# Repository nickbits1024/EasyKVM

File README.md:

# _Easy KVM_

## About Easy KVM

Easy KVM is a Wi-Fi enabled hybrid KVM.  It acts a an USB sharing switch and VESA DDC/CI switcher.  It does not touch the video signal which eliminates a lot of issues found with standard KVMs.

## Features

* Single USB 2.0 high speed capable port to be used with an external USB hub
* Wi-Fi control
* HDMI passthrough
* USB keyboard for macros and port switching
* Control monitor power state
* Integrated with Home Assistant

## External Requirements
* USB macro keypad e.g. [Amazon](https://www.amazon.com/gp/product/B09CKT8B7Y) [AliExpress](https://www.aliexpress.us/item/3256804248423460.html)
* USB 2.0 high speed hub e.g. [Amazon](https://www.amazon.com/gp/product/B005A0B3FG)
* Monitor with an HDMI port that supports VESA DDC/CI

## Port Setup
1. Connect source HDMI cable from video card to either one of the HDMI ports
2. Connect other HDMI port to monitor
3. Connect J1 Micro USB (top left) to PC1 USB
4. Connect J2 Micro USB (top right) to PC2 USB
5. Connect J6 Micro USB (bottom renter) to macro keypad
6. Connect J7 USB (bottom right) to USB hub
7. Connect J4 Micro USB (Center right) to either USB power or PC (for programming and serial monitoring)

## Wi-Fi Setup
Wi-Fi network selection is done through bluetooth.  
1. Download nRF Connect and connect to KVM
2. Open the client services tab and click Write Value the (up arrow) on the characteristic ending with an UUID of 29.  

3. Click the UTF-8 tab and enter the network SSID and click Write.

4. Click Write Value on the characteristic ending in 01.  This is the Wi-Fi password.  After clicking Write, the KVM should connect to the network.

## WebServer End Points

| URL | Method | Function | Payload |
| --- | ------ | -------- | ------- |
|/config|GET|Open configuration page||
|/monitor|GET|Return monitor state|`{	"on":	true }`|
|/monitor|POST|Set monitor state|`{	"on":	true }`|
|/kvm|GET|Return selected KVM port|`{ "kvm":	1 }`|
|/kvm/1|GET|Select KVM port 1||
|/kvm/2|GET|Select KVM port 2||

## Home Assistant
The KVM needs a Long-Lived Access Token to interact with home assistant.  Create one from the home assistant profile page and save it for later (e.g. notepad)

### Monitor Switch

Copy code below into the home assistant switches.yaml file.  This will create a switch in home assistant that can be used to turn the connected monitor on and off.
```
- platform: rest
  name: "Office Monitor"
  unique_id: 08a5830e-3309-4998-9d17-7ea7ecf154fd
  resource: http://<<KVM_HOST_NAME_OR_IP>>/monitor
  timeout: 30
  body_on: '{"on": true}'
  body_off: '{"on": false}'
  is_on_template: "{{ value_json.on }}"
  headers:
    Content-Type: application/json
```

## Configuration
1. Determine the IP of the KVM either from router UI or connecting the KVM to a computer and viewing the serial output.
2. Navigate to http://KVM_IP/config
3. Select the desired source and RGB led color for each input
4. Enter home assistant URL and previously created access token
5. Configure the macro keypad functions
6. Click save

Note clipboard import/export only work if you have the KVM behind an https proxy

## Usage
Once properly configured, the inputs can be switched using the configured macro keypad button or through the web server end points

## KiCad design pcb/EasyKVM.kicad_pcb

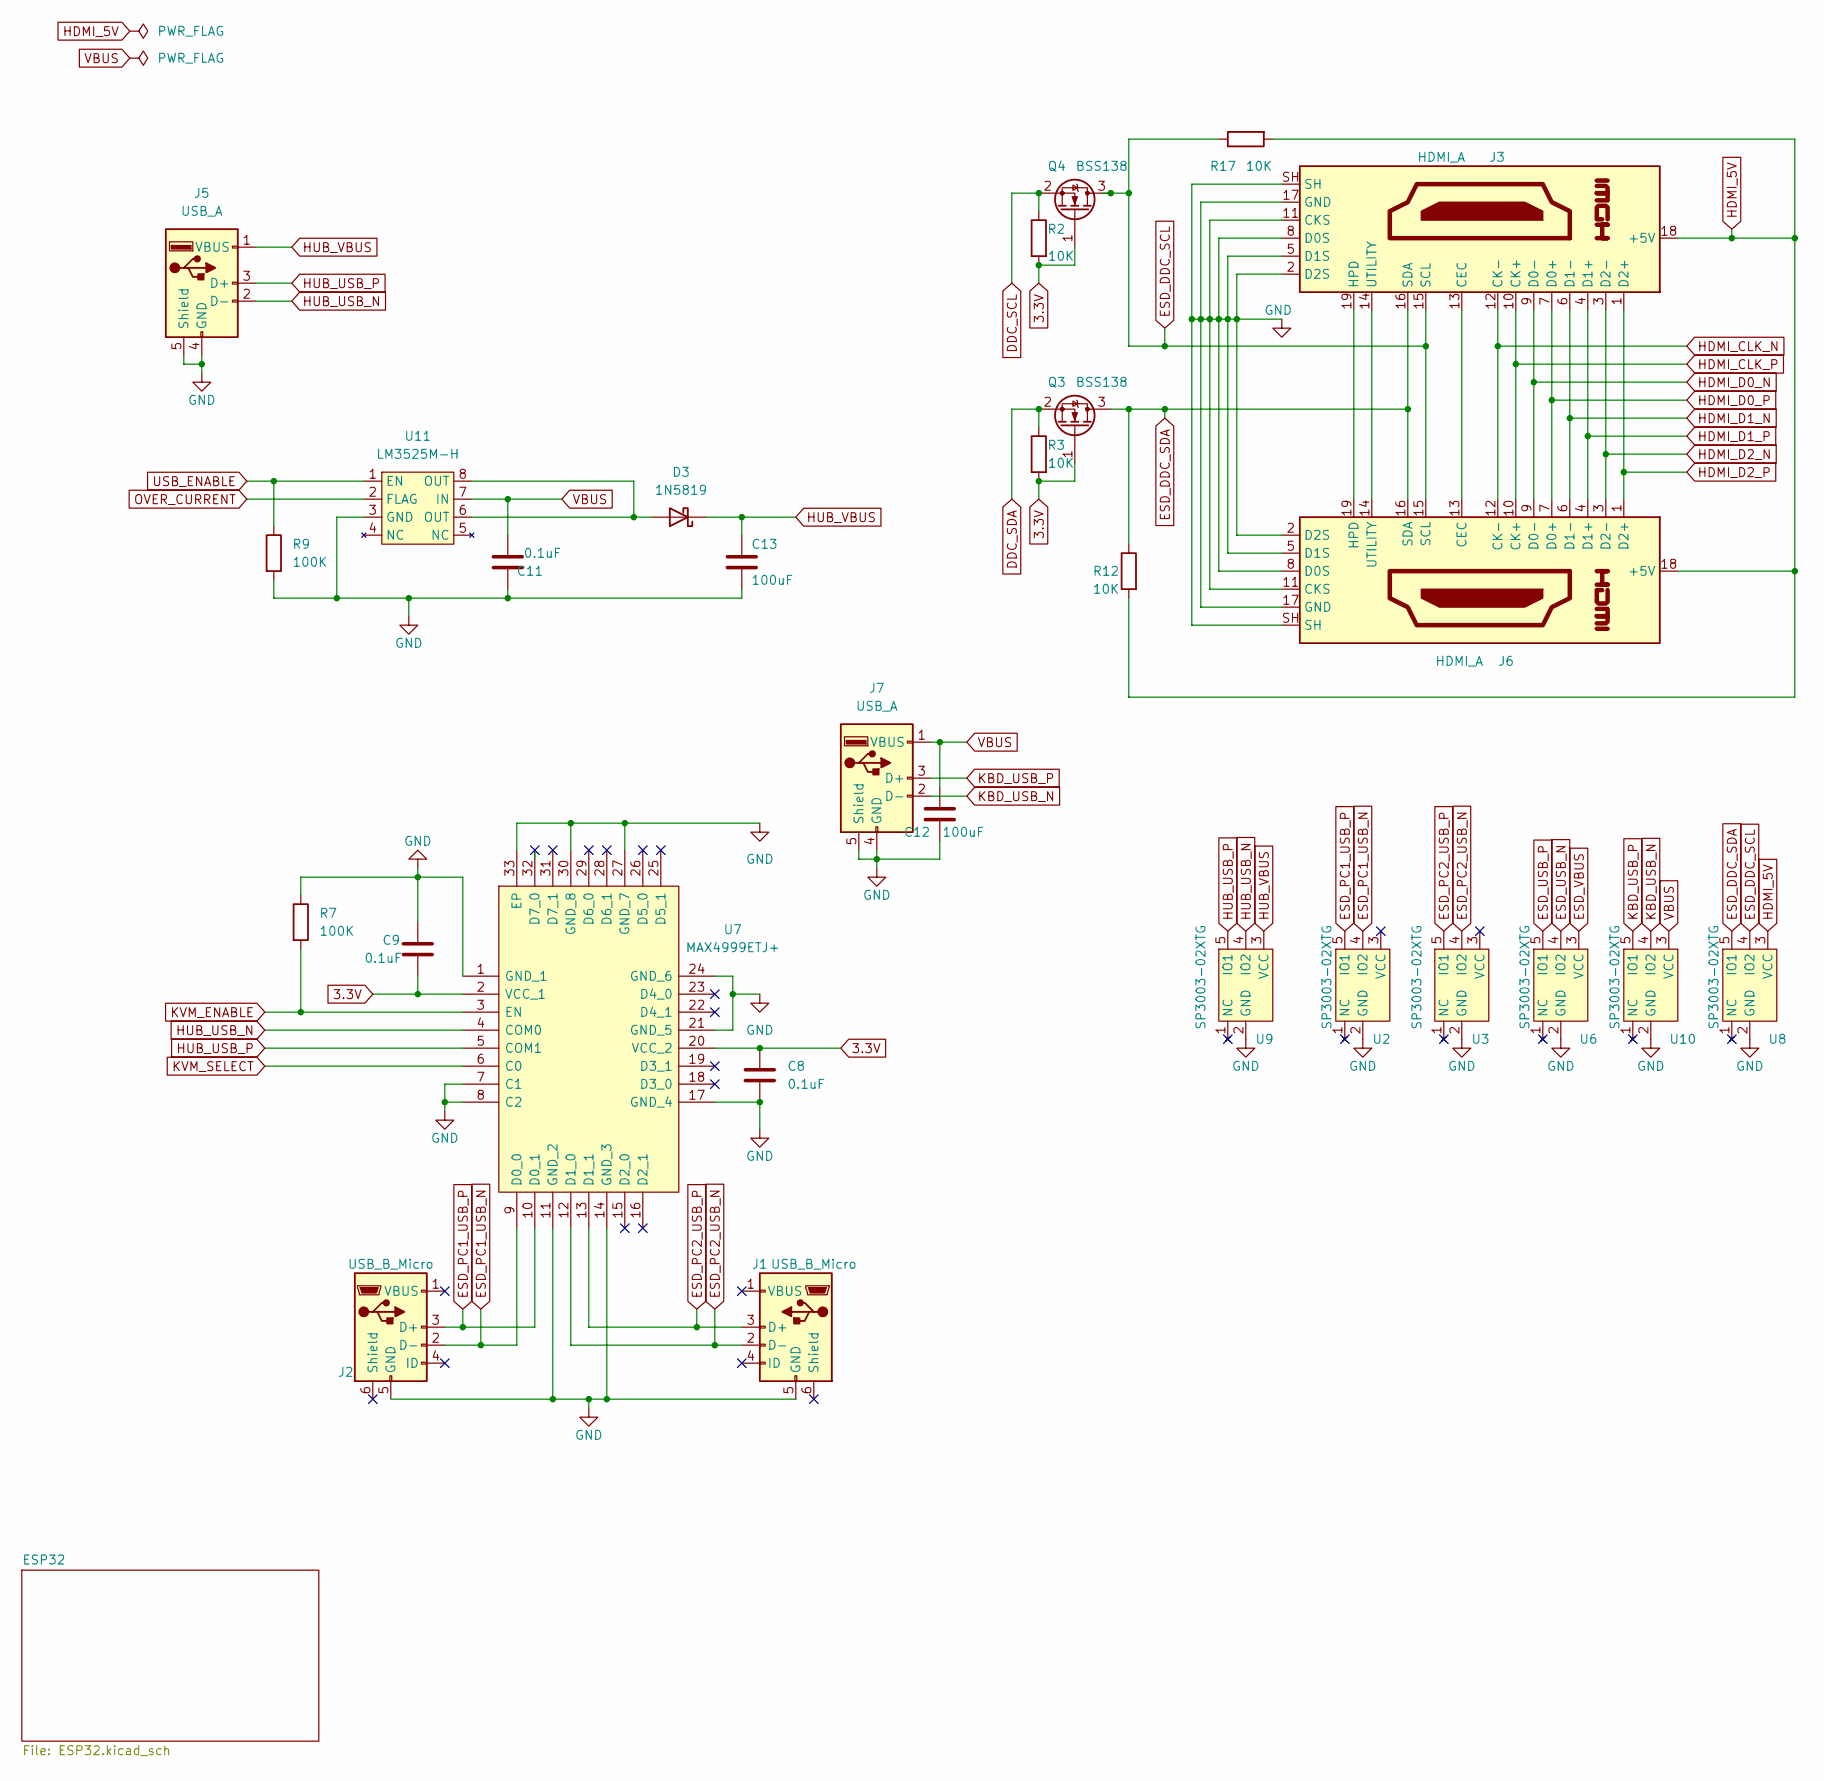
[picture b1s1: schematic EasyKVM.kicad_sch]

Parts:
C8, C9, C11: 0.1uF; C_0603_1608Metric
C12, C13: 100uF; C_1206_3216Metric
D3: 1N5819; D_SOD-323
J1, J2: USB_B_Micro; USB_Micro-B_Molex-105017-0001
J3, J6: HDMI_A; 2086581051
J5, J7: USB_A; USB_A_Molex_67643_Horizontal
Q3, Q4: BSS138; SOT-323_SC-70
R2, R3, R12, R17: 10K; R_0603_1608Metric
R7, R9: 100K; R_0603_1608Metric
U2, U3, U6, U8, U9, U10: SP3003-02XTG; Diodes_SOT-553
U7: MAX4999ETJ+; QFN50P500X500X80-33N; Manufacturer_Part_Number MAX4999ETJ+; Mouser Part Number 700-MAX4999ETJ
U11: LM3525M-H; SOIC-8_3.9x4.9mm_P1.27mm

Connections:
3.3V: C8.2, C9.1, Q3.1 (G), Q4.1 (G), R2.2, R3.2, U7.2 (VCC_1), U7.20 (VCC_2); also elsewhere on the board
DDC_SCL: Q4.2 (S), R2.1; also elsewhere on the board
DDC_SDA: Q3.2 (S), R3.1; also elsewhere on the board
ESD_DDC_SCL: J3.15 (SCL), J6.15 (SCL), Q4.3 (D), R17.1, U8.4 (IO2)
ESD_DDC_SDA: J3.16 (SDA), J6.16 (SDA), Q3.3 (D), R12.1, U8.5 (IO1)
ESD_PC1_USB_N: J2.2 (D-), U2.4 (IO2), U7.9 (D0_0)
ESD_PC1_USB_P: J2.3 (D+), U2.5 (IO1), U7.10 (D0_1)
ESD_PC2_USB_N: J1.2 (D-), U3.4 (IO2), U7.12 (D1_0)
ESD_PC2_USB_P: J1.3 (D+), U3.5 (IO1), U7.13 (D1_1)
ESD_USB_N: U6.4 (IO2); also elsewhere on the board
ESD_USB_P: U6.5 (IO1); also elsewhere on the board
ESD_VBUS: U6.3 (VCC); also elsewhere on the board
GND: C8.1, C9.2, C11.2, C12.2, C13.1, J1.5 (GND), J2.5 (GND), J3.2 (D2S), J3.5 (D1S), J3.8 (D0S), J3.11 (CKS), J3.17 (GND), J3.SH, J5.4 (GND), J5.5 (Shield), J6.2 (D2S), J6.5 (D1S), J6.8 (D0S), J6.11 (CKS), J6.17 (GND), J6.SH, J7.4 (GND), J7.5 (Shield), R7.1, R9.2, U2.2 (GND), U3.2 (GND), U6.2 (GND), U7.1 (GND_1), U7.7 (C1), U7.8 (C2), U7.11 (GND_2), U7.14 (GND_3), U7.17 (GND_4), U7.21 (GND_5), U7.24 (GND_6), U7.27 (GND_7), U7.30 (GND_8), U7.33 (EP), U8.2 (GND), U9.2 (GND), U10.2 (GND), U11.3 (GND); also elsewhere on the board
HDMI_5V: J3.18 (+5V), J6.18 (+5V), R12.2, R17.2, U8.3 (VCC)
HDMI_CLK_N: J3.12 (CK-), J6.12 (CK-)
HDMI_CLK_P: J3.10 (CK+), J6.10 (CK+)
HDMI_D0_N: J3.9 (D0-), J6.9 (D0-)
HDMI_D0_P: J3.7 (D0+), J6.7 (D0+)
HDMI_D1_N: J3.6 (D1-), J6.6 (D1-)
HDMI_D1_P: J3.4 (D1+), J6.4 (D1+)
HDMI_D2_N: J3.3 (D2-), J6.3 (D2-)
HDMI_D2_P: J3.1 (D2+), J6.1 (D2+)
HUB_USB_N: J5.2 (D-), U7.4 (COM0), U9.4 (IO2)
HUB_USB_P: J5.3 (D+), U7.5 (COM1), U9.5 (IO1)
HUB_VBUS: C13.2, D3.1 (K), J5.1 (VBUS), U9.3 (VCC)
KBD_USB_N: J7.2 (D-), U10.4 (IO2); also elsewhere on the board
KBD_USB_P: J7.3 (D+), U10.5 (IO1); also elsewhere on the board
KVM_ENABLE: R7.2, U7.3 (EN); also elsewhere on the board
KVM_SELECT: U7.6 (C0); also elsewhere on the board
unnamed: D3.2 (A), U11.6 (OUT), U11.8 (OUT)
unnamed: J3.13 (CEC), J6.13 (CEC)
unnamed: J3.14 (UTILITY), J6.14 (UTILITY)
unnamed: J3.19 (HPD), J6.19 (HPD)
OVER_CURRENT: U11.2 (FLAG); also elsewhere on the board
USB_ENABLE: R9.1, U11.1 (EN); also elsewhere on the board
VBUS: C11.1, C12.1, J7.1 (VBUS), U10.3 (VCC), U11.7 (IN); also elsewhere on the board

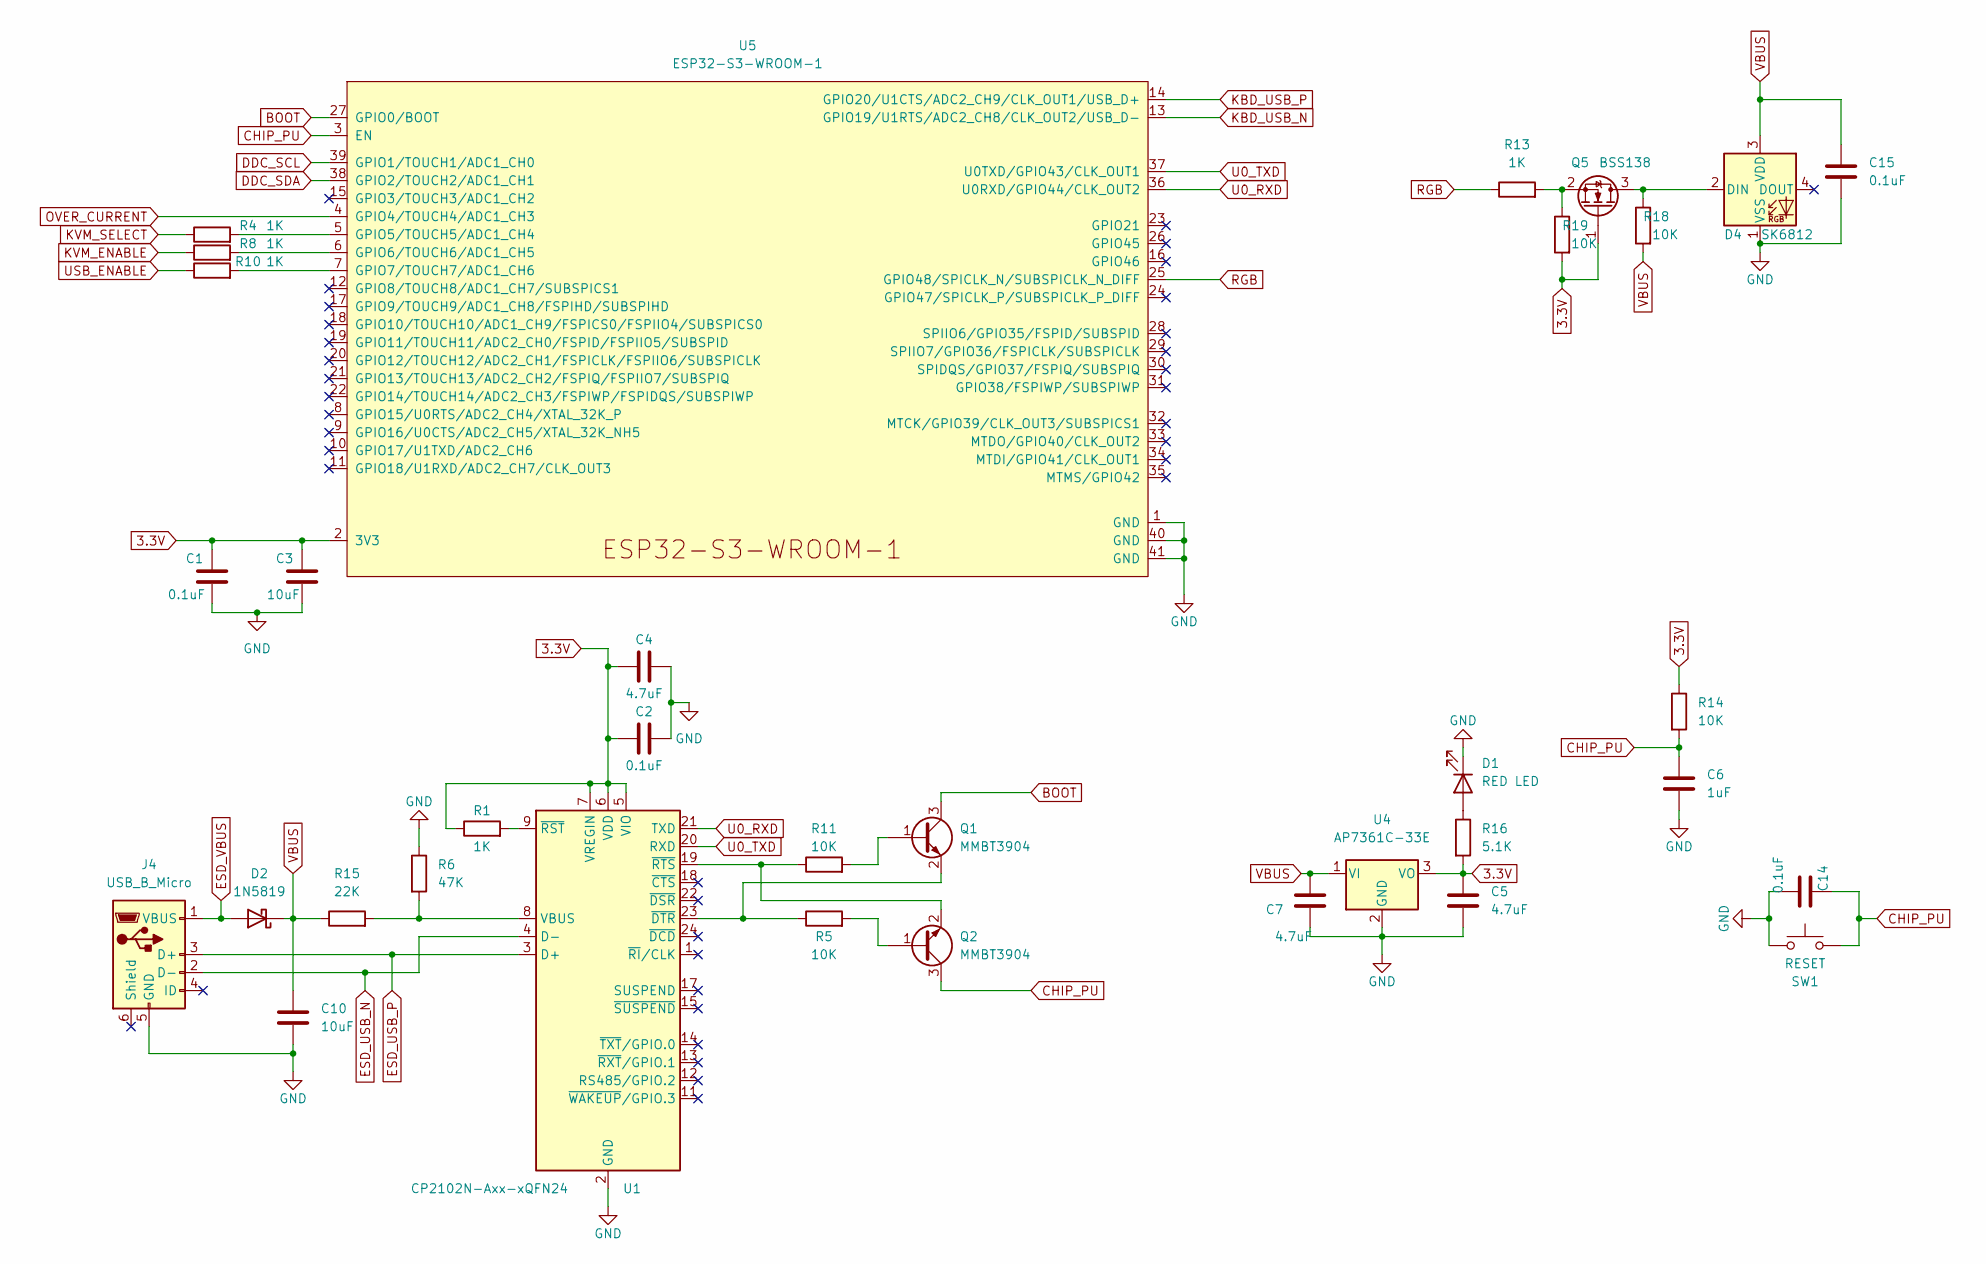
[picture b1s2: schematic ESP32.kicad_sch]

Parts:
C1, C2, C14, C15: 0.1uF; C_0603_1608Metric
C3, C10: 10uF; C_0603_1608Metric
C4, C5, C7: 4.7uF; C_0603_1608Metric
C6: 1uF; C_0603_1608Metric
D1: RED LED; LED_0603_1608Metric
D2: 1N5819; D_SOD-323
D4: SK6812; LED_SK6812_PLCC4_5.0x5.0mm_P3.2mm
J4: USB_B_Micro; USB_Micro-B_Molex-105017-0001
Q1, Q2: MMBT3904; SOT-23
Q5: BSS138; SOT-323_SC-70
R1, R4, R8, R10, R13: 1K; R_0603_1608Metric
R5, R11, R14, R18, R19: 10K; R_0603_1608Metric
R6: 47K; R_0603_1608Metric
R15: 22K; R_0603_1608Metric
R16: 5.1K; R_0603_1608Metric
SW1: RESET; SW_Push_1P1T_NO_6x6mm_H9.5mm
U1: CP2102N-Axx-xQFN24; QFN-24-1EP_4x4mm_P0.5mm_EP2.6x2.6mm
U4: AP7361C-33E; SOT-223-3_TabPin2
U5: ESP32-S3-WROOM-1

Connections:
3.3V: C1.1, C2.1, C3.1, C4.1, C5.2, Q5.1 (G), R1.1, R14.1, R16.2, R19.2, U1.5 (VIO), U1.6 (VDD), U1.7 (VREGIN), U4.3 (VO), U5.2 (3V3); also elsewhere on the board
BOOT: Q1.3 (C), U5.27 (GPIO0/BOOT)
CHIP_PU: C6.1, C14.1, Q2.3 (C), R14.2, SW1.2, U5.3 (EN)
DDC_SCL: U5.39 (GPIO1/TOUCH1/ADC1_CH0); also elsewhere on the board
DDC_SDA: U5.38 (GPIO2/TOUCH2/ADC1_CH1); also elsewhere on the board
ESD_USB_N: J4.2 (D-), U1.4 (D-); also elsewhere on the board
ESD_USB_P: J4.3 (D+), U1.3 (D+); also elsewhere on the board
ESD_VBUS: D2.2 (A), J4.1 (VBUS); also elsewhere on the board
GND: C1.2, C2.2, C3.2, C4.2, C5.1, C6.2, C7.1, C10.2, C14.2, C15.1, D1.1 (K), D4.1 (VSS), J4.5 (GND), R6.1, SW1.1, U1.2 (GND), U1.25 (GND), U4.2 (GND), U5.1 (GND), U5.40 (GND), U5.41 (GND); also elsewhere on the board
KBD_USB_N: U5.13 (GPIO19/U1RTS/ADC2_CH8/CLK_OUT2/USB_D-); also elsewhere on the board
KBD_USB_P: U5.14 (GPIO20/U1CTS/ADC2_CH9/CLK_OUT1/USB_D+); also elsewhere on the board
KVM_ENABLE: R8.1; also elsewhere on the board
KVM_SELECT: R4.1; also elsewhere on the board
unnamed: D1.2 (A), R16.1
unnamed: D4.2 (DIN), Q5.3 (D), R18.1
unnamed: Q1.1 (B), R11.2
unnamed: Q1.2 (E), R5.1, U1.23 (~DTR)
unnamed: Q2.1 (B), R5.2
unnamed: Q2.2 (E), R11.1, U1.19 (~RTS)
unnamed: Q5.2 (S), R13.2, R19.1
unnamed: R10.2, U5.7 (GPIO7/TOUCH7/ADC1_CH6)
unnamed: R8.2, U5.6 (GPIO6/TOUCH6/ADC1_CH5)
unnamed: R4.2, U5.5 (GPIO5/TOUCH5/ADC1_CH4)
unnamed: R1.2, U1.9 (~RST)
unnamed: R6.2, R15.2, U1.8 (VBUS)
OVER_CURRENT: U5.4 (GPIO4/TOUCH4/ADC1_CH3); also elsewhere on the board
RGB: R13.1, U5.25 (GPIO48/SPICLK_N/SUBSPICLK_N_DIFF)
U0_RXD: U1.21 (TXD), U5.36 (U0RXD/GPIO44/CLK_OUT2)
U0_TXD: U1.20 (RXD), U5.37 (U0TXD/GPIO43/CLK_OUT1)
USB_ENABLE: R10.1; also elsewhere on the board
VBUS: C7.2, C10.1, C15.2, D2.1 (K), D4.3 (VDD), R15.1, R18.2, U4.1 (VI); also elsewhere on the board

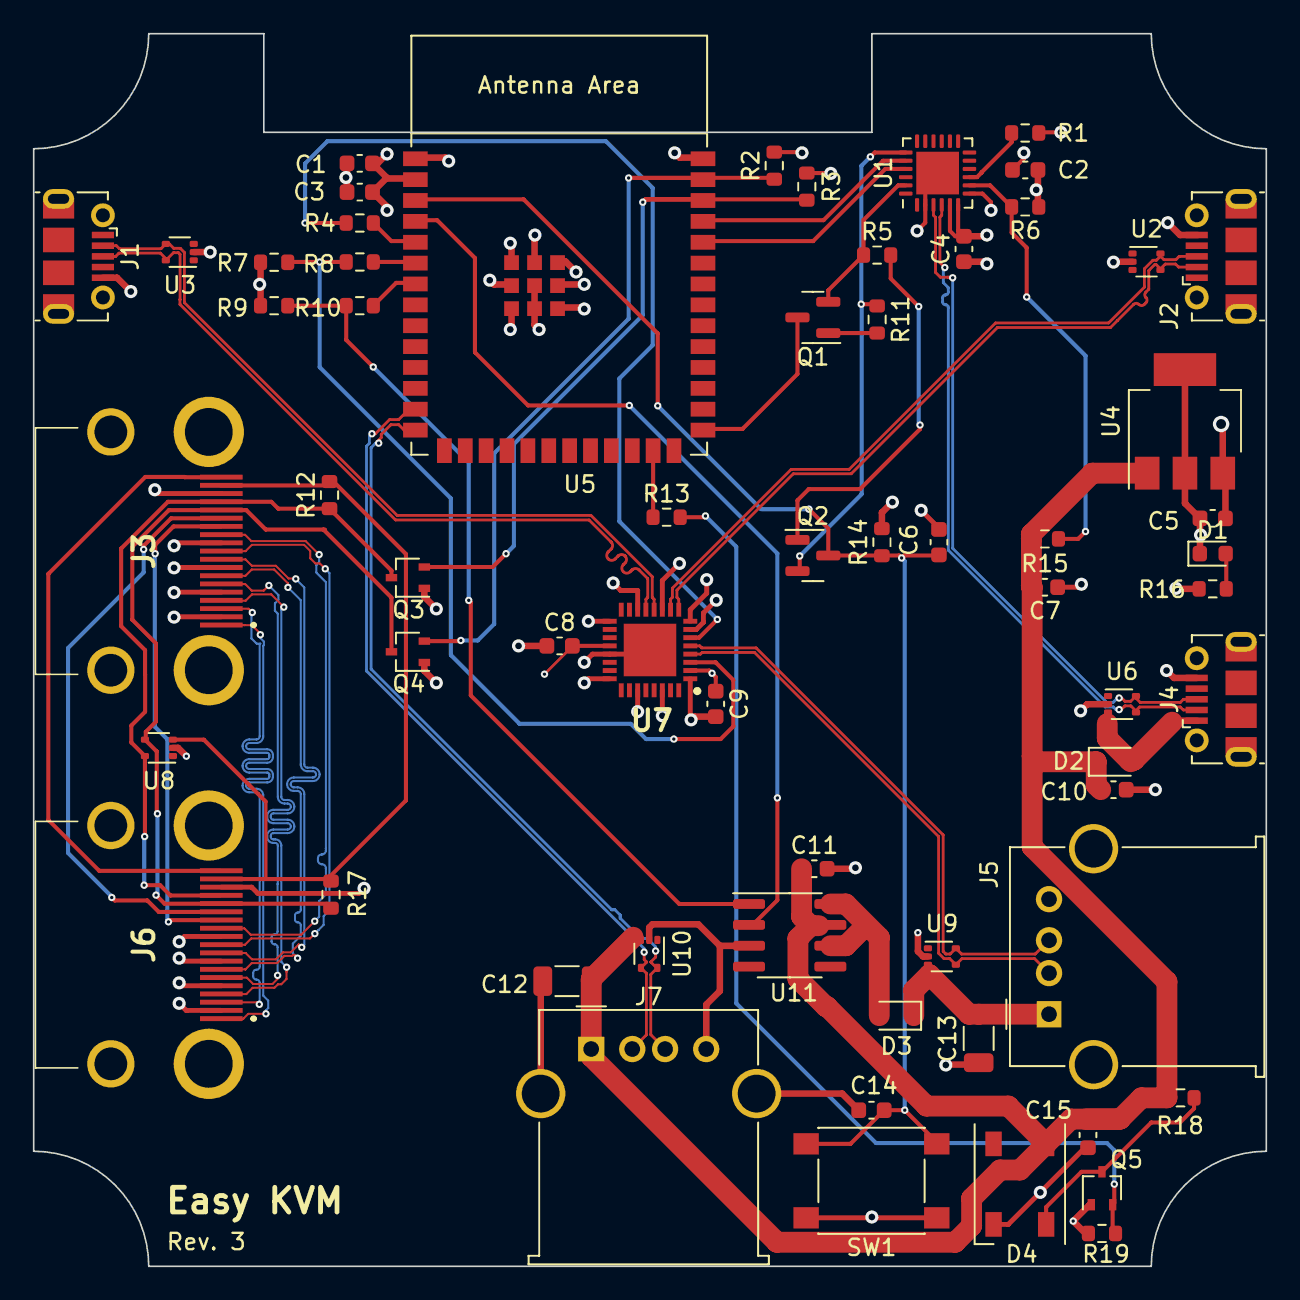
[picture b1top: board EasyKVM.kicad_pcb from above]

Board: 4 copper layers, 75.0 x 75.0 mm, 62 parts (0 on the bottom side), 53 nets.

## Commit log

2022-10-14 First version (mostly copied from PerfectKVM)
2022-10-21 over current check
2022-10-21 schematic w/o pull downs and start of pcb
2022-10-22 routing start
2022-10-25 pcb wip
2022-11-27 design bugs case update software bugs
2022-12-11 Fix cornerns Add hub diode R3
2022-12-15 new case
2022-12-15 health
2022-12-17 health logging
2022-12-23 tweaks
2022-12-23 esp-idf v5 upgrade
2023-01-03 docs
2023-07-09 usb resets lower ble advertising reorder references
2023-07-12 move (disabled) enable call after delay
